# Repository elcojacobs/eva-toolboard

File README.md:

# Nema 14/17 Toolboard for EVA

Breakout board for EVA to mount to the back of a Nema 17 or name 17 motor. (31mm hole spacing or 43.8mm diagonally).

All signals and power are routed over 2 20p ribbon cables.
For the heater, 5 parallel wires are used to provide enough current. For part fan power, 2 parallel wires are used.

The same board is mounted at the hotend and near the main board.
On the main board side, most components are not mounted, only the connectors.
On the hotend side, all components are mounted except the terminal block in the middle.

## Features
- Everything wired through 2 ribbon cables.
- Spring terminal blocks for: heater, part fan, tool fan, probe, neopixel, aux 1-3
- ADXL345 on board
- Chamber temp PT1000 on board
- Neopixel LED on board and daisy chained to output terminal block
- 3 unused AUX signals

## Jumpers
- On the hotend side, connect 1 of the solder jumpers to select the voltage for the probe
- For correct neopixel routing, connect the hotend solder jumpers on the hotend side and the board solder jumpers on the main board side.

## License
Shield: [![CC BY-NC-SA 4.0][cc-by-nc-sa-shield]][cc-by-nc-sa]

This work is licensed under a
[Creative Commons Attribution-NonCommercial-ShareAlike 4.0 International License][cc-by-nc-sa].

[![CC BY-NC-SA 4.0][cc-by-nc-sa-image]][cc-by-nc-sa]

[cc-by-nc-sa]: http://creativecommons.org/licenses/by-nc-sa/4.0/
[cc-by-nc-sa-image]: https://licensebuttons.net/l/by-nc-sa/4.0/88x31.png
[cc-by-nc-sa-shield]: https://img.shields.io/badge/License-CC%20BY--NC--SA%204.0-lightgrey.svg

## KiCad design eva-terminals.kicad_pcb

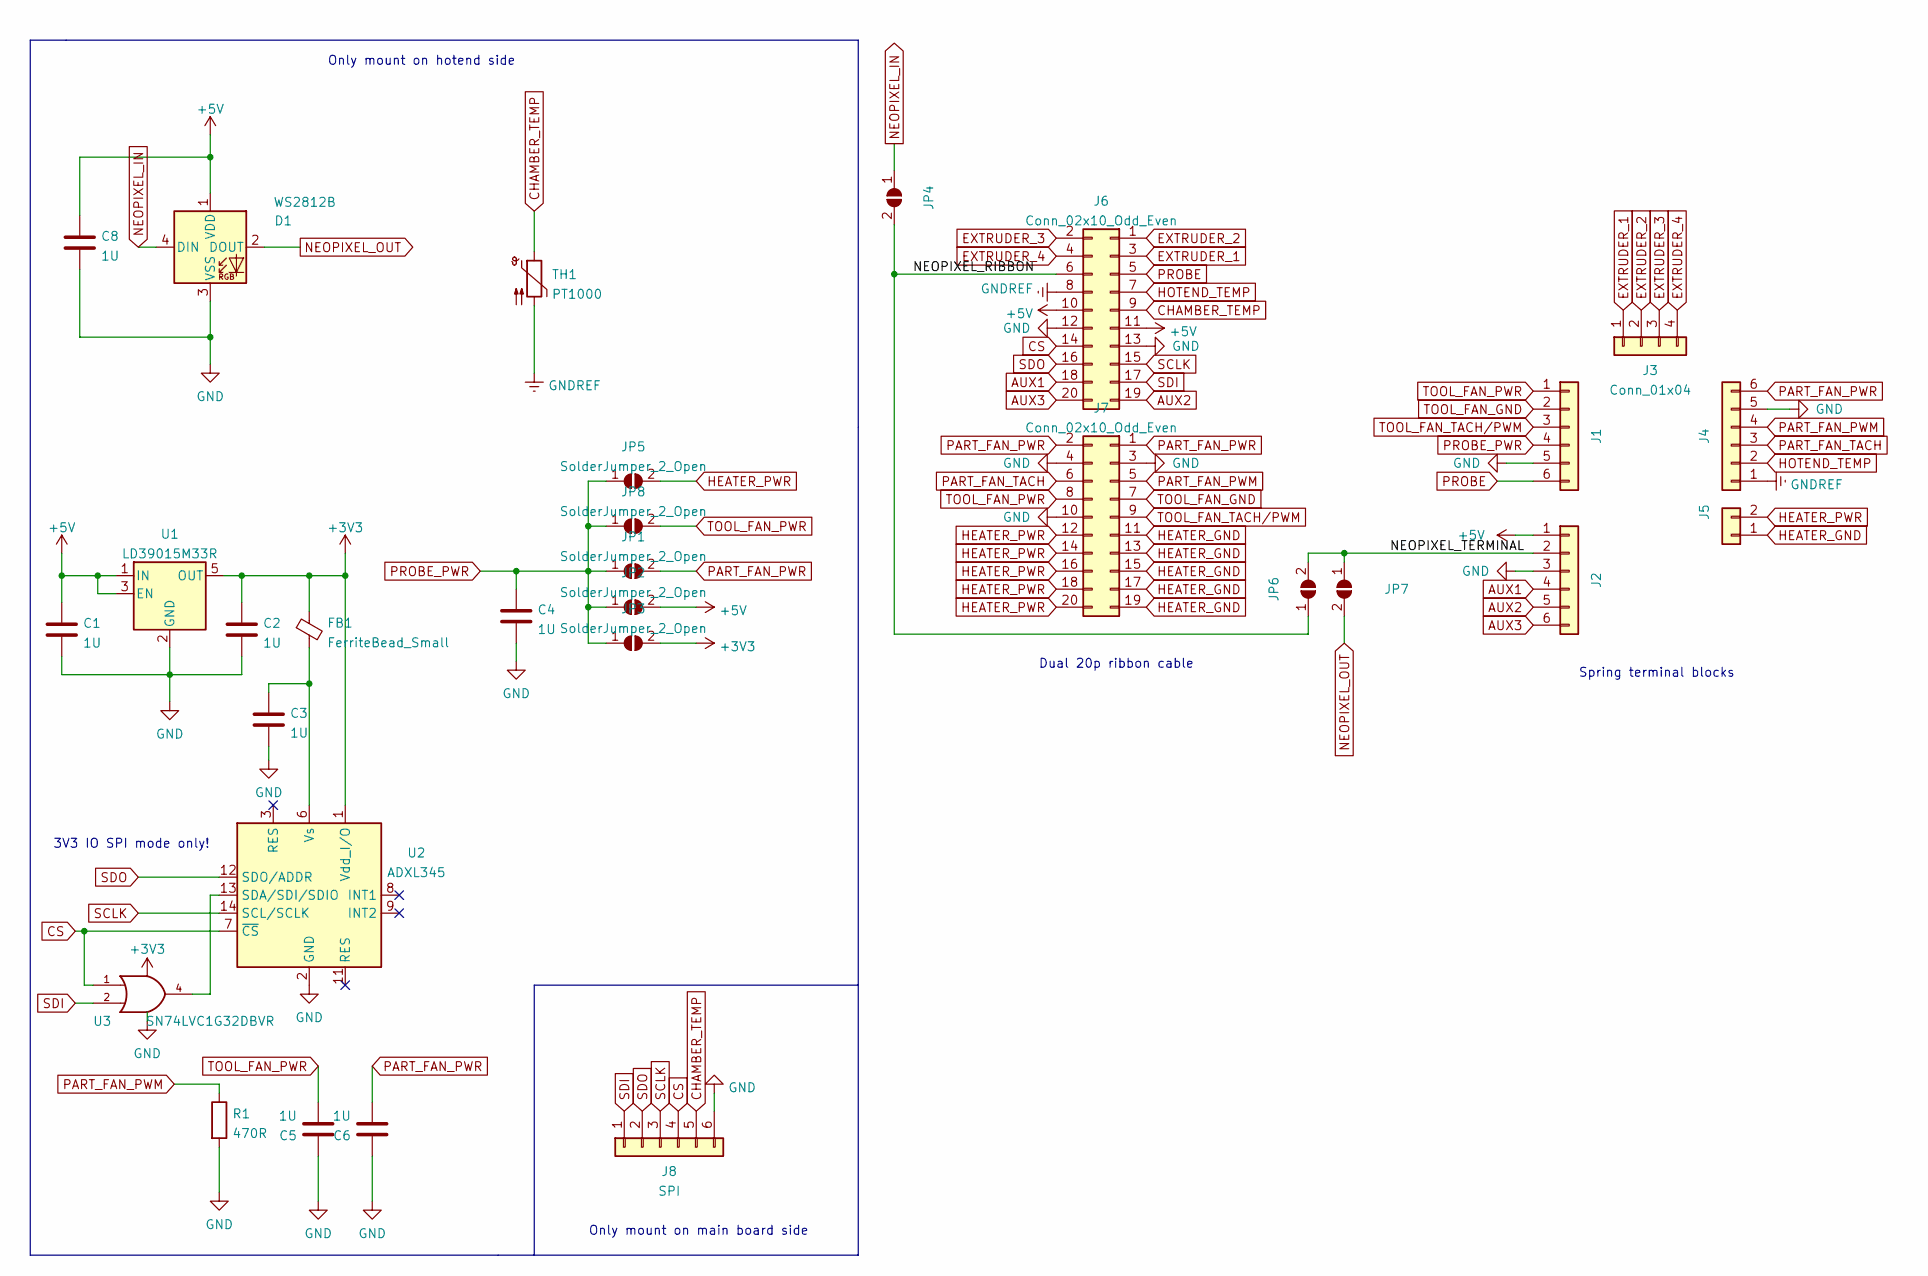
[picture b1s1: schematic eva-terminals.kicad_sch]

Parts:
C1, C2, C3, C4, C5, C6, C8: 1U; C_0805_2012Metric
D1: WS2812B; LED_WS2812B_PLCC4_5.0x5.0mm_P3.2mm
FB1: FerriteBead_Small; L_0603_1608Metric
J1, J2, J4: 691403900006B
J3: Conn_01x04; JST_XH_S4B-XH-A_1x04_P2.50mm_Horizontal
J5: HEATER; 691401700002B
J6, J7: Conn_02x10_Odd_Even; 690367292076
J8: SPI; 691403900006B
JP1, JP2, JP3, JP4, JP5, JP6, JP7, JP8: SolderJumper_2_Open; SolderJumper-2_P1.3mm_Open_RoundedPad1.0x1.5mm
R1: 470R; R_0603_1608Metric
TH1: PT1000; R_1206_3216Metric
U1: LD39015M33R; SOT-23-5
U2: ADXL345; LGA-14_3x5mm_P0.8mm_LayoutBorder1x6y
U3: SN74LVC1G32DBVR‎; SOT-23-5

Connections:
+3V3: C2.1, FB1.1, JP3.2 (B), U1.5 (OUT), U2.1 (Vdd_I/O), U3.5 (VCC)
+5V: C1.1, C8.1, D1.1 (VDD), J2.1, J2.A1 (Pin_1A), J6.10, J6.11, JP2.2 (B), U1.1 (IN), U1.3 (EN)
/NEOPIXEL_RIBBON: J6.6, JP4.2 (B), JP6.1 (A)
/NEOPIXEL_TERMINAL: J2.2, J2.A2, JP6.2 (B), JP7.1 (A)
AUX1: J2.4, J2.A4, J6.18
AUX2: J2.5, J2.A5, J6.19
AUX3: J2.6, J2.A6, J6.20
CHAMBER_TEMP: J6.9, J8.5, J8.A5, TH1.1
CS: J6.14, J8.4, J8.A4, U2.7 (~CS), U3.1
EXTRUDER_1: J3.1, J6.3
EXTRUDER_2: J3.2, J6.1
EXTRUDER_3: J3.3, J6.2
EXTRUDER_4: J3.4, J6.4
GND: C1.2, C2.2, C3.2, C4.2, C5.1, C6.1, C8.2, D1.3 (VSS), J1.5, J1.A5, J2.3, J2.A3 (Pin_3), J4.5, J4.A5, J6.12, J6.13, J7.3, J7.4, J7.10, J8.6, J8.A6, R1.2, U1.2 (GND), U2.2 (GND), U2.4 (GND), U2.5 (GND), U3.3 (GND)
GNDREF: J4.1, J4.A1 (Pin_1A), J6.8, TH1.2
HEATER_GND: J5.1, J5.A1 (Pin_1A), J7.11, J7.13, J7.15, J7.17, J7.19
HEATER_PWR: J5.2, J5.A2, J7.12, J7.14, J7.16, J7.18, J7.20, JP5.2 (B)
HOTEND_TEMP: J4.2, J4.A2, J6.7
NEOPIXEL_IN: D1.4 (DIN), JP4.1 (A)
NEOPIXEL_OUT: D1.2 (DOUT), JP7.2 (B)
unnamed: C3.1, FB1.2, U2.6 (Vs)
unnamed: U2.13 (SDA/SDI/SDIO), U3.4
PART_FAN_PWM: J4.4, J4.A4, J7.5, R1.1
PART_FAN_PWR: C6.2, J4.6, J4.A6, J7.1, J7.2, JP1.2 (B)
PART_FAN_TACH: J4.3, J4.A3 (Pin_3), J7.6
PROBE: J1.6, J1.A6, J6.5
PROBE_PWR: C4.1, J1.4, J1.A4, JP1.1 (A), JP2.1 (A), JP3.1 (A), JP5.1 (A), JP8.1 (A)
SCLK: J6.15, J8.3, J8.A3 (Pin_3), U2.14 (SCL/SCLK)
SDI: J6.17, J8.1, J8.A1 (Pin_1A), U3.2
SDO: J6.16, J8.2, J8.A2, U2.12 (SDO/ADDR)
TOOL_FAN_GND: J1.2, J1.A2, J7.7
TOOL_FAN_PWR: C5.2, J1.1, J1.A1 (Pin_1A), J7.8, JP8.2 (B)
TOOL_FAN_TACH/PWM: J1.3, J1.A3 (Pin_3), J7.9

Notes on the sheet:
Only mount on main board side
Only mount on hotend side
Spring terminal blocks
3V3 IO SPI mode only!
Dual 20p ribbon cable

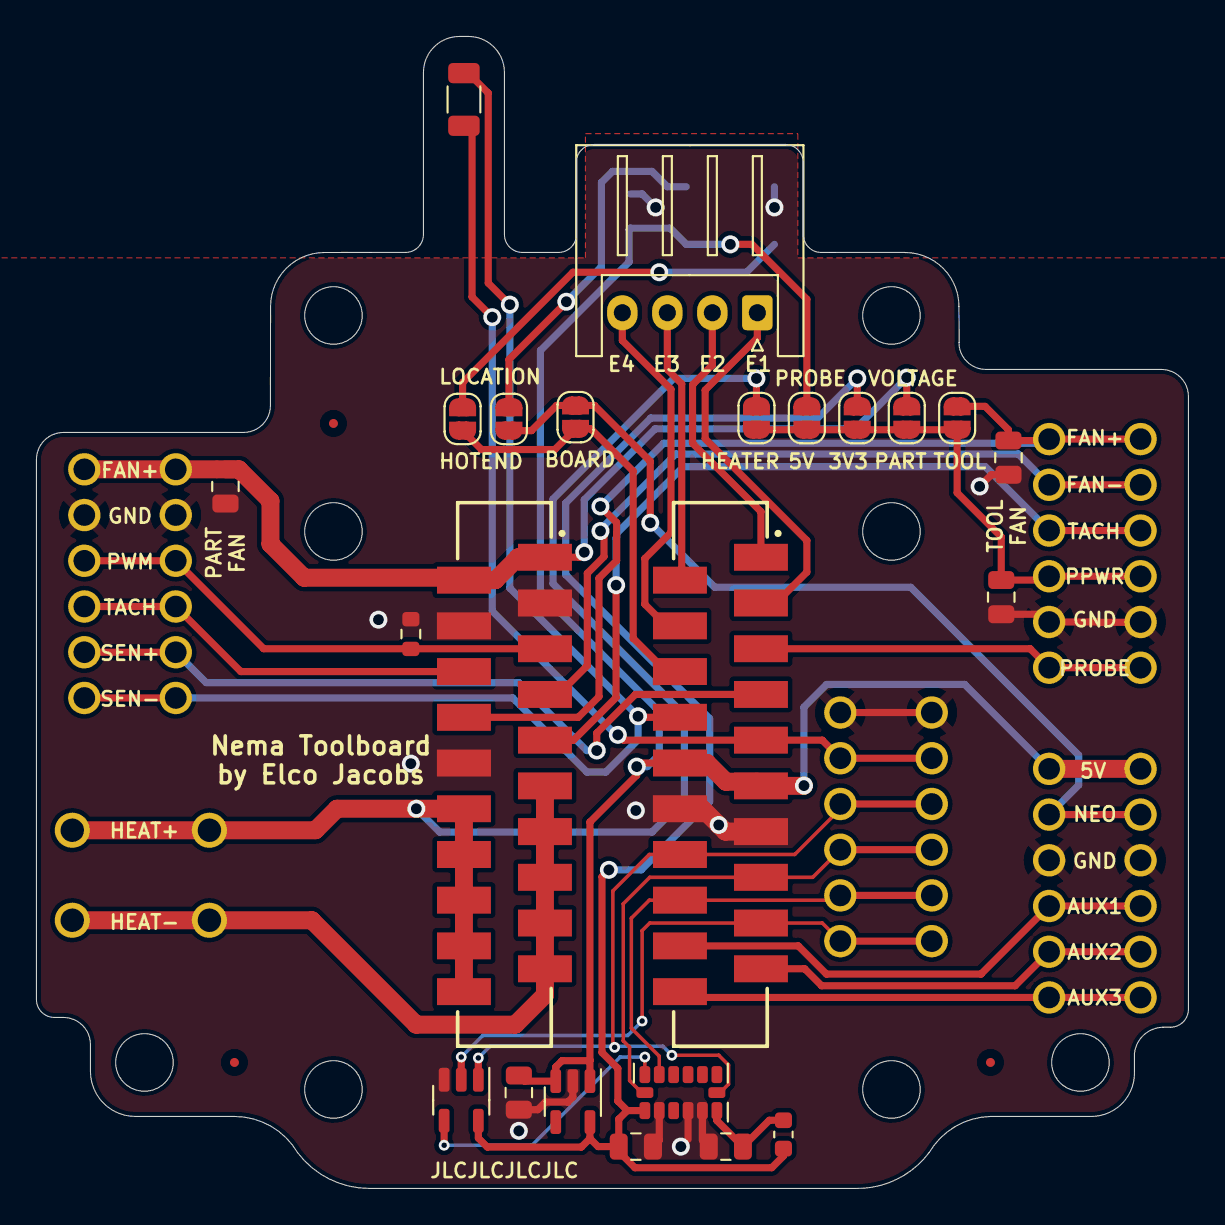
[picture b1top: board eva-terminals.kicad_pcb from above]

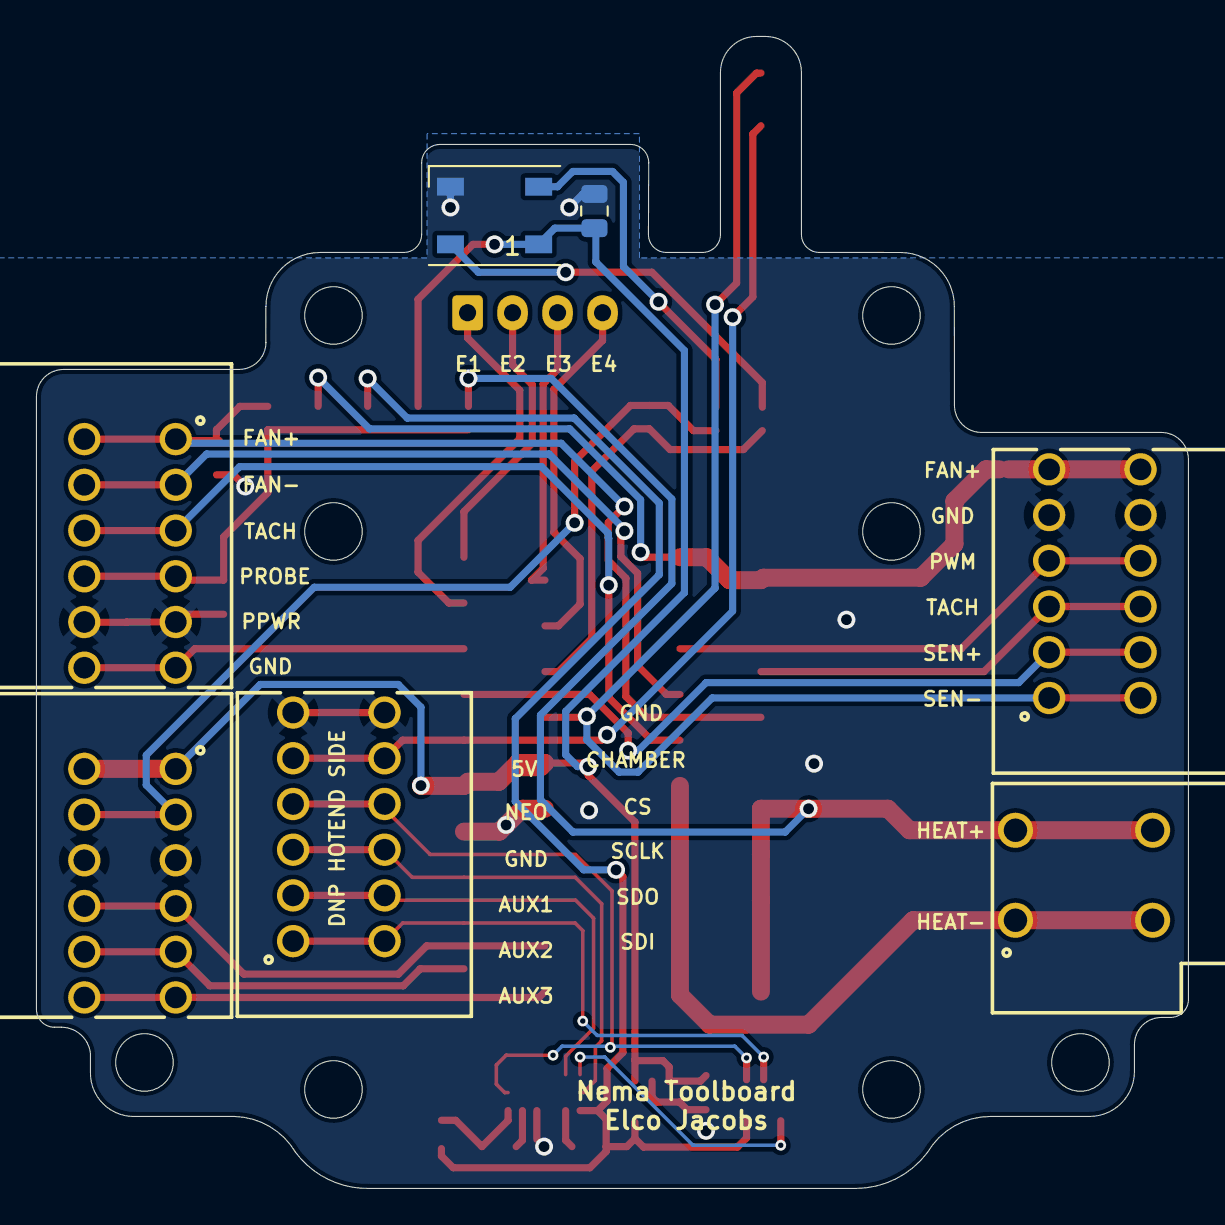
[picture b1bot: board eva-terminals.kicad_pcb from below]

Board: 2 copper layers, 64.0 x 64.0 mm, 30 parts (7 on the bottom side), 33 nets.

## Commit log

2022-01-13 initial commit wip
2022-01-15 wip dual ribbon
2022-01-17 finalized board layout rev 1
2022-01-17 Added README
2022-01-17 add license
2022-01-17 more clearance for LGX bracket
2022-01-19 jst-xh for stepper
2022-01-19 change footprint for OR gate
2022-01-20 add heater voltage to selection for probe
2022-01-21 removed unncessary via in groundref
2022-01-21 add fiducial
2022-01-21 small changes
